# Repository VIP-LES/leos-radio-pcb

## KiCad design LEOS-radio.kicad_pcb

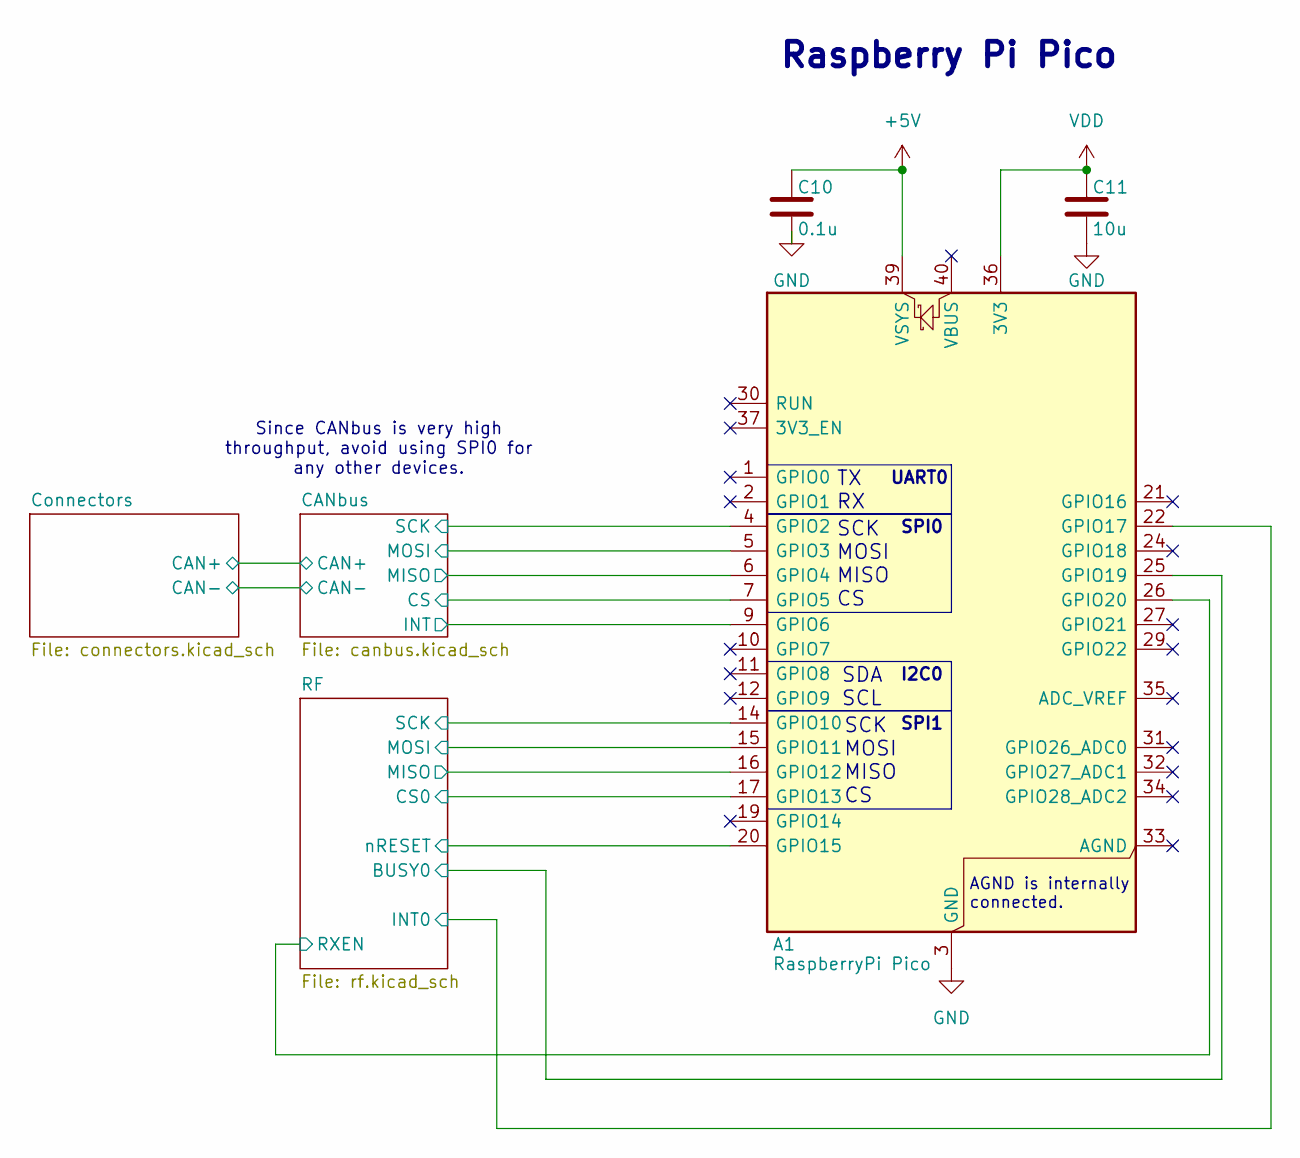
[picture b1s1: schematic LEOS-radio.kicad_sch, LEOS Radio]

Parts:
A1: RaspberryPi Pico; RaspberryPi_Pico_Common_THT; MPN PIM724; Digikey 1778-PIM724-ND
C10: 0.1u; C_0603_1608Metric; MPN CL10B104KB8NNNL; Digikey 1276-CL10B104KB8NNNLCT-ND
C11: 10u; C_0805_2012Metric; MPN CL21B106KOQNNNE; Digikey 1276-2872-1-ND

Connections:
+5V: A1.39 (VSYS), C10.1; also elsewhere on the board
/CANbus/CS: A1.7 (GPIO5); also elsewhere on the board
/CANbus/INT: A1.9 (GPIO6); also elsewhere on the board
/CANbus/MISO: A1.6 (GPIO4); also elsewhere on the board
/CANbus/MOSI: A1.5 (GPIO3); also elsewhere on the board
/CANbus/SCK: A1.4 (GPIO2); also elsewhere on the board
/RF/BUSY0: A1.25 (GPIO19); also elsewhere on the board
/RF/CS0: A1.17 (GPIO13); also elsewhere on the board
/RF/INT0: A1.22 (GPIO17); also elsewhere on the board
/RF/MISO: A1.16 (GPIO12); also elsewhere on the board
/RF/MOSI: A1.15 (GPIO11); also elsewhere on the board
/RF/RXEN: A1.26 (GPIO20); also elsewhere on the board
/RF/SCK: A1.14 (GPIO10); also elsewhere on the board
/RF/nRESET: A1.20 (GPIO15); also elsewhere on the board
GND: A1.3 (GND), A1.8 (GND), A1.13 (GND), A1.18 (GND), A1.23 (GND), A1.28 (GND), A1.38 (GND), C10.2, C11.2; also elsewhere on the board
VDD: A1.36 (3V3), C11.1; also elsewhere on the board

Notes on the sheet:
SPI1
Raspberry Pi Pico
SCK MOSI MISO CS
Since CANbus is very high throughput, avoid using SPI0 for any other devices.
SPI0
SDA SCL
TX RX
UART0
I2C0
AGND is internally connected.

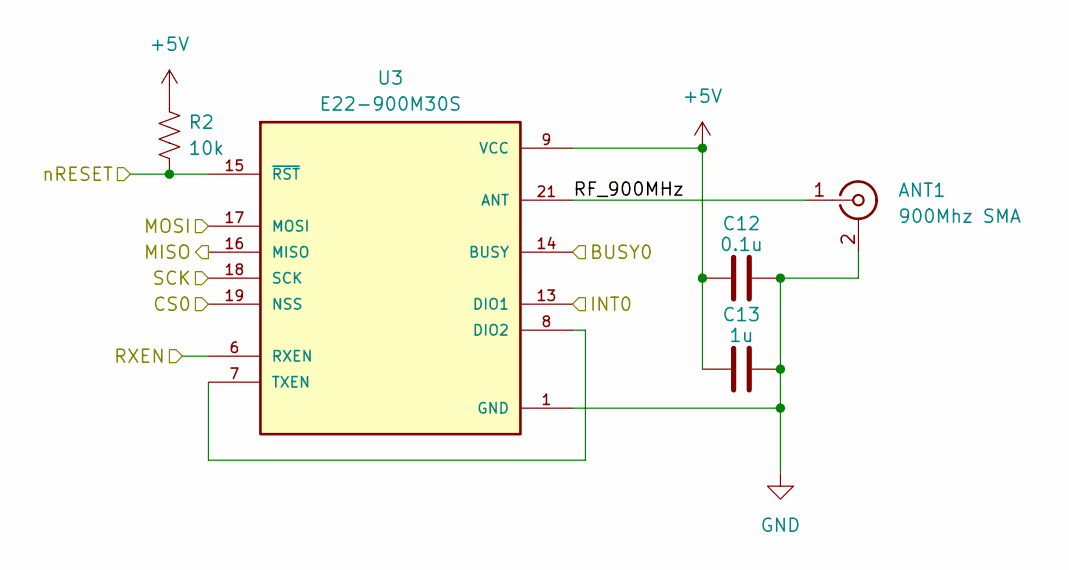
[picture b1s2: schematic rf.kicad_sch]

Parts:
ANT1: 900Mhz SMA; SMA_Molex_73251-1153_EdgeMount_Horizontal; MPN 0732511153; Digikey 900-0732511153-ND
C12: 0.1u; C_0603_1608Metric; MPN CL10B104KB8NNNL; Digikey 1276-CL10B104KB8NNNLCT-ND
C13: 1u; C_0603_1608Metric; MPN CL10B105KA8NNNC; Digikey 1276-1184-1-ND
R2: 10k; R_0805_2012Metric; MPN CRCW080510K0FKEA; Digikey 541-10.0KCCT-ND
U3: E22-900M30S; XCVR_E22-900M30S; MPN E22-900M30S

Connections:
+5V: C12.1, C13.1, R2.1, U3.9 (VCC), U3.10 (VCC); also elsewhere on the board
/RF/BUSY0: U3.14 (BUSY); also elsewhere on the board
/RF/CS0: U3.19 (NSS); also elsewhere on the board
/RF/INT0: U3.13 (DIO1); also elsewhere on the board
/RF/MISO: U3.16 (MISO); also elsewhere on the board
/RF/MOSI: U3.17 (MOSI); also elsewhere on the board
/RF/RF_900MHz: ANT1.1 (In), U3.21 (ANT)
/RF/RXEN: U3.6 (RXEN); also elsewhere on the board
/RF/SCK: U3.18 (SCK); also elsewhere on the board
/RF/nRESET: R2.2, U3.15 (~RST); also elsewhere on the board
GND: ANT1.2 (Ext), C12.2, C13.2, U3.1 (GND), U3.2 (GND), U3.3 (GND), U3.4 (GND), U3.5 (GND), U3.11 (GND), U3.12 (GND), U3.20 (GND), U3.22 (GND); also elsewhere on the board
unnamed: U3.7 (TXEN), U3.8 (DIO2)

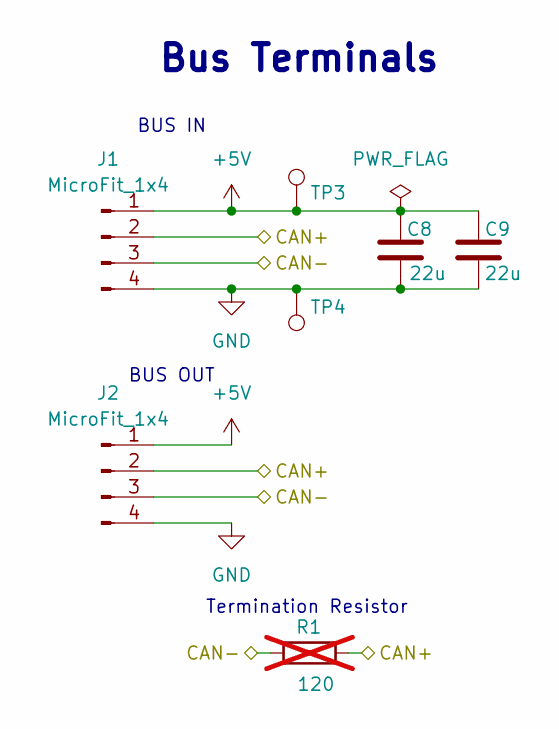
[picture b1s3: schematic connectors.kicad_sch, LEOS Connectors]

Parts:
C8, C9: 22u; C_0805_2012Metric; MPN CL21A226MAYNNNE; Digikey 1276-CL21A226MAYNNNECT-ND
J1, J2: MicroFit_1x4; Molex_MicroFit3.0_43650-0410_1x04_Horizontal; MPN 0436500409; Digikey WM1882CT-ND
R1: 120; R_Axial_DIN0207_L6.3mm_D2.5mm_P7.62mm_Horizontal; MPN CFR-25JR-52-120R; Digikey 13-CFR-25JR-52-120RCT-ND; not fitted
TP3: 5V Test Point; TestPoint_Loop_D2.60mm_Drill0.9mm_Beaded; MPN 5000; Digikey 36-5000-ND
TP4: GND Test Point; TestPoint_Loop_D2.60mm_Drill0.9mm_Beaded; MPN 5001; Digikey 36-5001-ND

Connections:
+5V: C8.1, C9.1, J1.1, J2.1, TP3.1 (1_1); also elsewhere on the board
/CANbus/CAN+: J1.2, J2.2, R1.2; also elsewhere on the board
/CANbus/CAN-: J1.3, J2.3, R1.1; also elsewhere on the board
GND: C8.2, C9.2, J1.4, J2.4, TP4.1 (1_1); also elsewhere on the board

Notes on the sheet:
BUS OUT
Bus Terminals
BUS IN
Termination Resistor

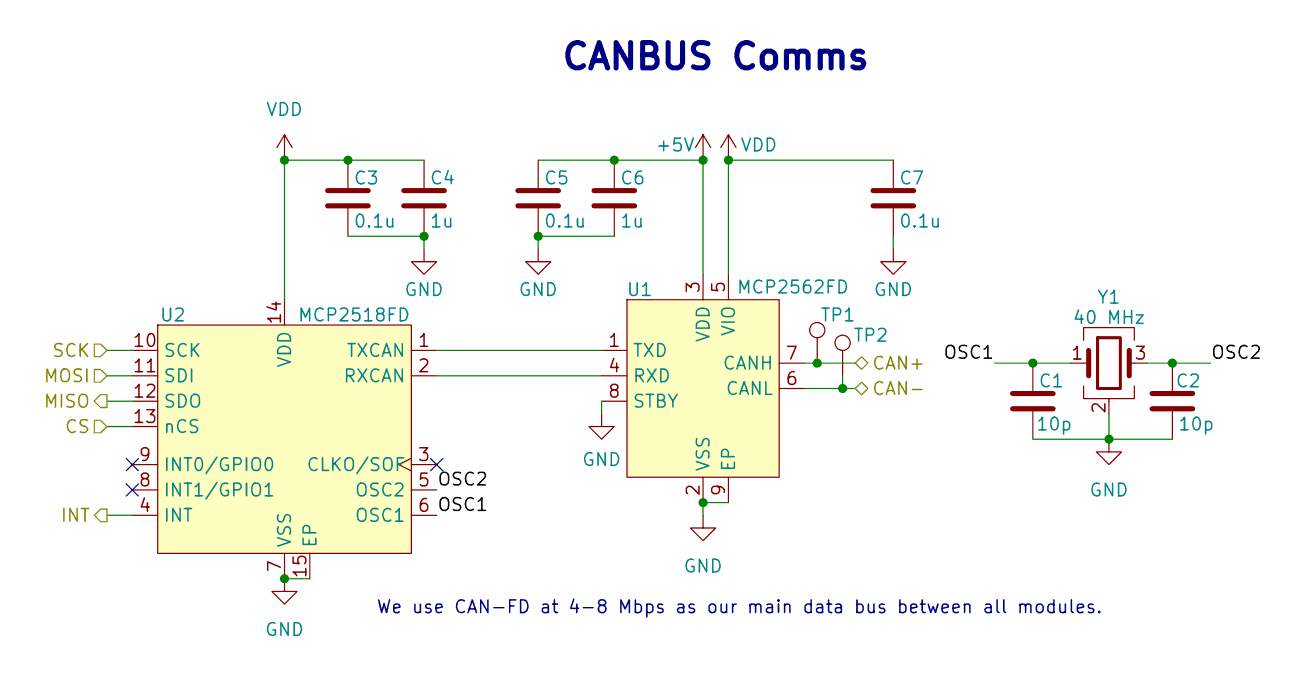
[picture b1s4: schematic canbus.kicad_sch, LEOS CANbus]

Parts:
C1, C2: 10p; C_0603_1608Metric; MPN CL10C100JB8NNNC; Digikey 1276-1027-1-ND
C3, C5, C7: 0.1u; C_0603_1608Metric; MPN CL10B104KB8NNNL; Digikey 1276-CL10B104KB8NNNLCT-ND
C4, C6: 1u; C_0603_1608Metric; MPN CL10B105KA8NNNC; Digikey 1276-1184-1-ND
TP1: CAN-H Test Point; TestPoint_Loop_D2.60mm_Drill0.9mm_Beaded; MPN 5004; Digikey 36-5004-ND
TP2: CAN-L Test Point; TestPoint_Loop_D2.60mm_Drill0.9mm_Beaded; MPN 5116; Digikey 36-5116-ND
U1: MCP2562FD; SOIC-8_3.9x4.9mm_P1.27mm; MPN MCP2562FDT-E/SN; LCSC C511335
U2: MCP2518FD; SOIC-14_3.9x8.7mm_P1.27mm; MPN MCP2518FDT-E/SL; LCSC C626758
Y1: 40 MHz; Crystal_SMD_2016-4Pin_2.0x1.6mm; MPN ECS-400-10-37B2-CKY-TR; Digikey 50-ECS-400-10-37B2-CKY-TRCT-ND

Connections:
+5V: C5.1, C6.1, U1.3 (VDD); also elsewhere on the board
/CANbus/CAN+: TP1.1 (1_1), U1.7 (CANH); also elsewhere on the board
/CANbus/CAN-: TP2.1 (1_1), U1.6 (CANL); also elsewhere on the board
/CANbus/CS: U2.13 (nCS); also elsewhere on the board
/CANbus/INT: U2.4 (INT); also elsewhere on the board
/CANbus/MISO: U2.12 (SDO); also elsewhere on the board
/CANbus/MOSI: U2.11 (SDI); also elsewhere on the board
/CANbus/OSC1: C1.2, U2.6 (OSC1), Y1.1
/CANbus/OSC2: C2.2, U2.5 (OSC2), Y1.3
/CANbus/SCK: U2.10 (SCK); also elsewhere on the board
GND: C1.1, C2.1, C3.2, C4.2, C5.2, C6.2, C7.2, U1.2 (VSS), U1.8 (STBY), U1.9 (EP), U2.7 (VSS), U2.15 (EP), Y1.2 (G), Y1.4 (G); also elsewhere on the board
unnamed: U1.4 (RXD), U2.2 (RXCAN)
unnamed: U1.1 (TXD), U2.1 (TXCAN)
VDD: C3.1, C4.1, C7.1, U1.5 (VIO), U2.14 (VDD); also elsewhere on the board

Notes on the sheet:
CANBUS Comms
We use CAN-FD at 4-8 Mbps as our main data bus between all modules.

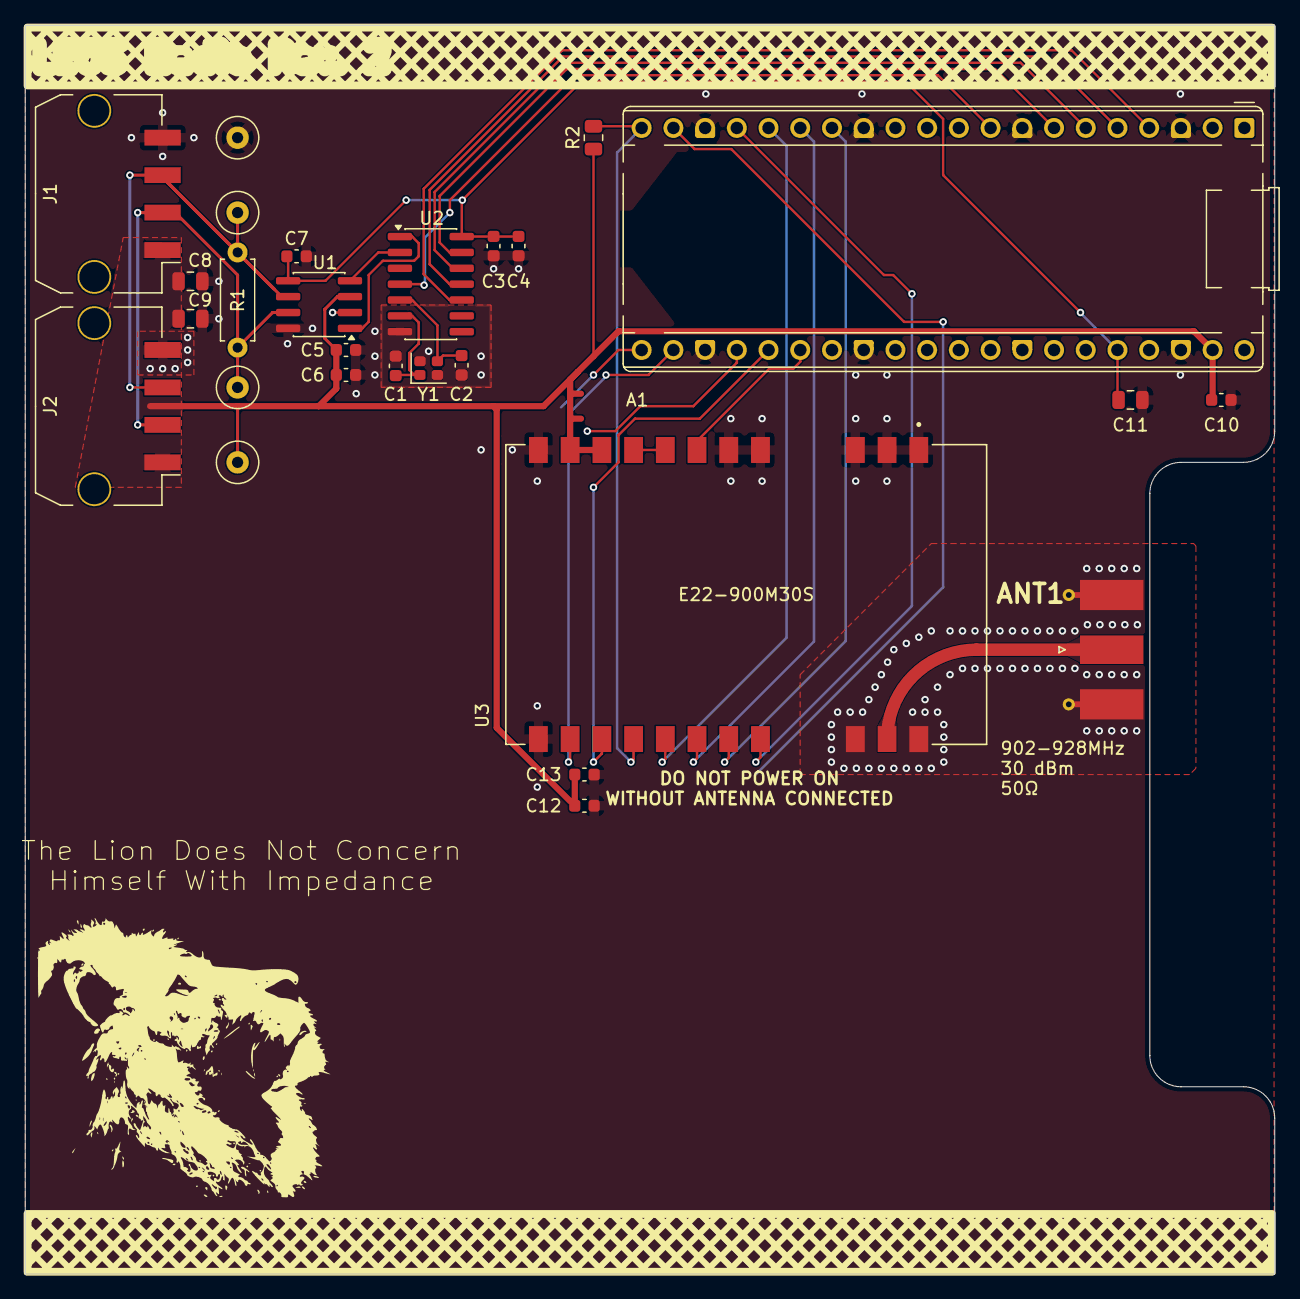
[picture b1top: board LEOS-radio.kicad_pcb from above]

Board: 2 copper layers, 100.1 x 100.0 mm, 27 parts (0 on the bottom side), 24 nets.

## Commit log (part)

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2026-02-17 Add .gitignore for KiCad and backup files
2026-02-18 update file names
2026-02-18 v2 with dual 1W LoRa transcievers, edge-mount SMA connectors, and an all new design
2026-02-18 Fix backwards ANT labels and increase font size
